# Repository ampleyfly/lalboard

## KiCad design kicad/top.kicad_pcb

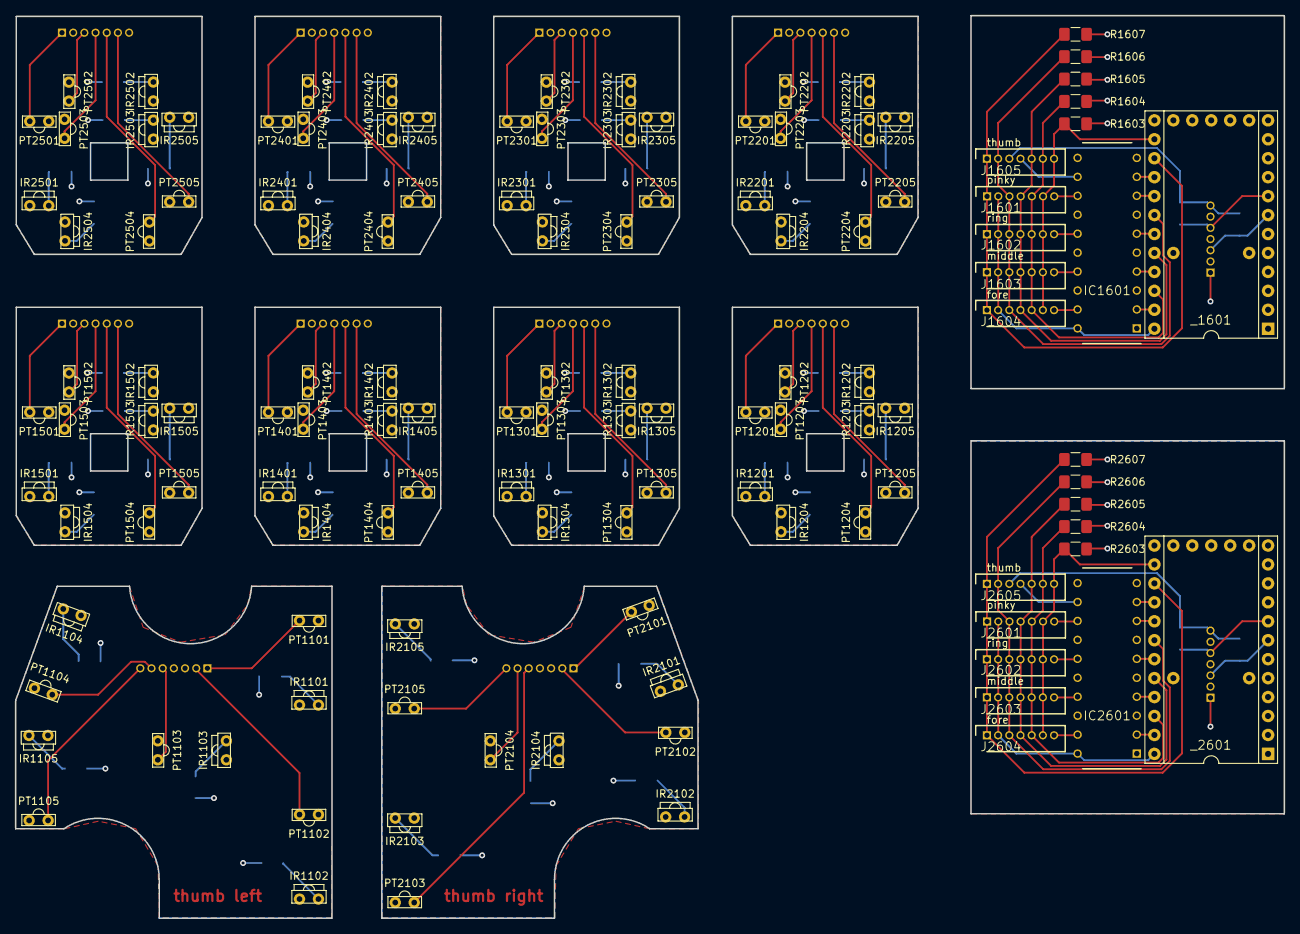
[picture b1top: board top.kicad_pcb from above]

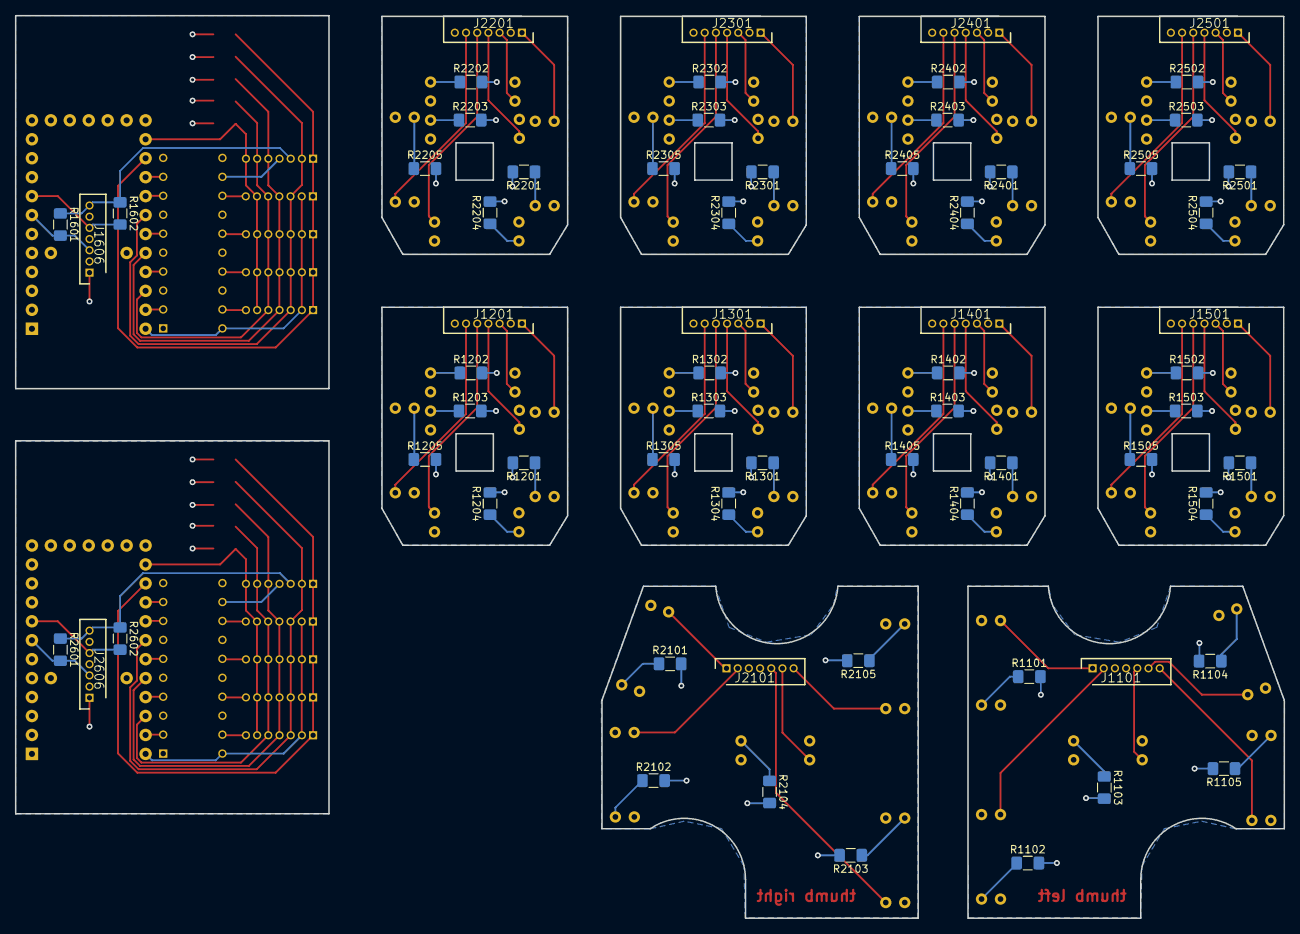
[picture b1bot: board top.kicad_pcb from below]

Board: 4 copper layers, 170.1 x 121.0 mm, 190 parts (66 on the bottom side), 160 nets.

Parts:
IC1601, IC2601: TLC59211IN; DIP794W53P254L2540H508Q20N
IR1101, IR1102, IR1103, IR1104, IR1105, IR1201, IR1202, IR1203, IR1204, IR1205, IR1301, IR1302, IR1303, IR1304, IR1305, IR1401, IR1402, IR1403, IR1404, IR1405, IR1501, IR1502, IR1503, IR1504, IR1505, IR2101, IR2102, IR2103, IR2104, IR2105, IR2201, IR2202, IR2203, IR2204, IR2205, IR2301, IR2302, IR2303, IR2304, IR2305, IR2401, IR2402, IR2403, IR2404, IR2405, IR2501, IR2502, IR2503, IR2504, IR2505: IR928-6C-F
J1101, J1201, J1301, J1401, J1501, J2101, J2201, J2301, J2401, J2501: Conn_01x07_Female; SHDR7W50P0X150_1X7_1200X350X45
J1601, J1602, J1603, J1604, J1605, J1606, J2601, J2602, J2603, J2604, J2605, J2606: B7B-ZR_(LF)(SN); SHDR7W50P0X150_1X7_1200X350X45
PT1101, PT1102, PT1103, PT1104, PT1105, PT1201, PT1202, PT1203, PT1204, PT1205, PT1301, PT1302, PT1303, PT1304, PT1305, PT1401, PT1402, PT1403, PT1404, PT1405, PT1501, PT1502, PT1503, PT1504, PT1505, PT2101, PT2102, PT2103, PT2104, PT2105, PT2201, PT2202, PT2203, PT2204, PT2205, PT2301, PT2302, PT2303, PT2304, PT2305, PT2401, PT2402, PT2403, PT2404, PT2405, PT2501, PT2502, PT2503, PT2504, PT2505: PT908-7B-F
R1101, R1102, R1103, R1104, R1105, R1201, R1202, R1203, R1204, R1205, R1301, R1302, R1303, R1304, R1305, R1401, R1402, R1403, R1404, R1405, R1501, R1502, R1503, R1504, R1505, R2101, R2102, R2103, R2104, R2105, R2201, R2202, R2203, R2204, R2205, R2301, R2302, R2303, R2304, R2305, R2401, R2402, R2403, R2404, R2405, R2501, R2502, R2503, R2504, R2505: 150; R_1206_3216Metric_Pad1.42x1.75mm_HandSolder
R1601, R1602, R1603, R1604, R1605, R1606, R1607, R2601, R2602, R2603, R2604, R2605, R2606, R2607: 2k; R_1206_3216Metric_Pad1.42x1.75mm_HandSolder
_1601, _2601: TEENSY

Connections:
/center_left/+5V: J1605.3, J1606.7, R1601.1, R1602.1, _1601.5V2
/center_left/F+5V: IC1601.20, J1601.2, J1602.2, J1603.2, J1604.2, _1601.+5V
/center_left/FD: J1601.4, J1602.4, J1603.4, J1604.4, J1605.5, R1605.1, _1601.F5
/center_left/FE: J1601.6, J1602.6, J1603.6, J1604.6, J1605.7, R1603.1, _1601.D7
/center_left/FGND: IC1601.19, J1604.7
/center_left/FN: J1601.3, J1602.3, J1603.3, J1604.3, J1605.2, R1606.1, _1601.F7
/center_left/FS: J1601.5, J1602.5, J1603.5, J1604.5, J1605.6, R1604.1, _1601.F1
/center_left/FW: J1601.1, J1602.1, J1603.1, J1604.1, J1605.1, R1607.1, _1601.B4
/center_left/GND: IC1601.3, IC1601.5, IC1601.7, IC1601.11, J1606.1, R1603.2, R1604.2, R1605.2, R1606.2, R1607.2, _1601.GND
/center_left/MGND: IC1601.17, J1603.7
/center_left/PGND: IC1601.13, J1601.7
/center_left/RGND: IC1601.15, J1602.7
/center_left/SCL: J1606.3, R1601.2, _1601.D0
/center_left/SDA: J1606.5, R1602.2, _1601.D1
/center_left/TGND: IC1601.12, J1605.4
/center_right/+5V: J2605.3, J2606.7, R2601.1, R2602.1, _2601.5V2
/center_right/F+5V: IC2601.20, J2601.2, J2602.2, J2603.2, J2604.2, _2601.+5V
/center_right/FD: J2601.4, J2602.4, J2603.4, J2604.4, J2605.5, R2605.1, _2601.F5
/center_right/FE: J2601.6, J2602.6, J2603.6, J2604.6, J2605.7, R2603.1, _2601.D7
/center_right/FGND: IC2601.19, J2604.7
/center_right/FN: J2601.3, J2602.3, J2603.3, J2604.3, J2605.2, R2606.1, _2601.F7
/center_right/FS: J2601.5, J2602.5, J2603.5, J2604.5, J2605.6, R2604.1, _2601.F1
/center_right/FW: J2601.1, J2602.1, J2603.1, J2604.1, J2605.1, R2607.1, _2601.B4
/center_right/GND: IC2601.3, IC2601.5, IC2601.7, IC2601.11, J2606.1, R2603.2, R2604.2, R2605.2, R2606.2, R2607.2, _2601.GND
/center_right/MGND: IC2601.17, J2603.7
/center_right/PGND: IC2601.13, J2601.7
/center_right/RGND: IC2601.15, J2602.7
/center_right/SCL: J2606.3, R2601.2, _2601.D0
/center_right/SDA: J2606.5, R2602.2, _2601.D1
/center_right/TGND: IC2601.12, J2605.4
/index_left/+5V: IR1201.2, IR1202.2, IR1203.2, IR1204.2, IR1205.2, J1201.2, PT1201.1, PT1202.1, PT1203.1, PT1204.1, PT1205.1
/index_left/D: J1201.4, PT1203.2
/index_left/E: J1201.6, PT1205.2
/index_left/GND: J1201.7, R1201.2, R1202.2, R1203.2, R1204.2, R1205.2
/index_left/N: J1201.3, PT1202.2
/index_left/S: J1201.5, PT1204.2
/index_left/W: J1201.1, PT1201.2
/index_right/+5V: IR2201.2, IR2202.2, IR2203.2, IR2204.2, IR2205.2, J2201.2, PT2201.1, PT2202.1, PT2203.1, PT2204.1, PT2205.1
/index_right/D: J2201.4, PT2203.2
/index_right/E: J2201.6, PT2205.2
/index_right/GND: J2201.7, R2201.2, R2202.2, R2203.2, R2204.2, R2205.2
/index_right/N: J2201.3, PT2202.2
/index_right/S: J2201.5, PT2204.2
/index_right/W: J2201.1, PT2201.2
/middle_left/+5V: IR1301.2, IR1302.2, IR1303.2, IR1304.2, IR1305.2, J1301.2, PT1301.1, PT1302.1, PT1303.1, PT1304.1, PT1305.1
/middle_left/D: J1301.4, PT1303.2
/middle_left/E: J1301.6, PT1305.2
/middle_left/GND: J1301.7, R1301.2, R1302.2, R1303.2, R1304.2, R1305.2
/middle_left/N: J1301.3, PT1302.2
/middle_left/S: J1301.5, PT1304.2
/middle_left/W: J1301.1, PT1301.2
/middle_right/+5V: IR2301.2, IR2302.2, IR2303.2, IR2304.2, IR2305.2, J2301.2, PT2301.1, PT2302.1, PT2303.1, PT2304.1, PT2305.1
/middle_right/D: J2301.4, PT2303.2
/middle_right/E: J2301.6, PT2305.2
/middle_right/GND: J2301.7, R2301.2, R2302.2, R2303.2, R2304.2, R2305.2
/middle_right/N: J2301.3, PT2302.2
/middle_right/S: J2301.5, PT2304.2
/middle_right/W: J2301.1, PT2301.2
/pinky_left/+5V: IR1501.2, IR1502.2, IR1503.2, IR1504.2, IR1505.2, J1501.2, PT1501.1, PT1502.1, PT1503.1, PT1504.1, PT1505.1
/pinky_left/D: J1501.4, PT1503.2
/pinky_left/E: J1501.6, PT1505.2
/pinky_left/GND: J1501.7, R1501.2, R1502.2, R1503.2, R1504.2, R1505.2
/pinky_left/N: J1501.3, PT1502.2
/pinky_left/S: J1501.5, PT1504.2
/pinky_left/W: J1501.1, PT1501.2
/pinky_right/+5V: IR2501.2, IR2502.2, IR2503.2, IR2504.2, IR2505.2, J2501.2, PT2501.1, PT2502.1, PT2503.1, PT2504.1, PT2505.1
/pinky_right/D: J2501.4, PT2503.2
/pinky_right/E: J2501.6, PT2505.2
/pinky_right/GND: J2501.7, R2501.2, R2502.2, R2503.2, R2504.2, R2505.2
/pinky_right/N: J2501.3, PT2502.2
/pinky_right/S: J2501.5, PT2504.2
/pinky_right/W: J2501.1, PT2501.2
/ring_left/+5V: IR1401.2, IR1402.2, IR1403.2, IR1404.2, IR1405.2, J1401.2, PT1401.1, PT1402.1, PT1403.1, PT1404.1, PT1405.1
/ring_left/D: J1401.4, PT1403.2
/ring_left/E: J1401.6, PT1405.2
/ring_left/GND: J1401.7, R1401.2, R1402.2, R1403.2, R1404.2, R1405.2
/ring_left/N: J1401.3, PT1402.2
/ring_left/S: J1401.5, PT1404.2
/ring_left/W: J1401.1, PT1401.2
/ring_right/+5V: IR2401.2, IR2402.2, IR2403.2, IR2404.2, IR2405.2, J2401.2, PT2401.1, PT2402.1, PT2403.1, PT2404.1, PT2405.1
/ring_right/D: J2401.4, PT2403.2
/ring_right/E: J2401.6, PT2405.2
/ring_right/GND: J2401.7, R2401.2, R2402.2, R2403.2, R2404.2, R2405.2
/ring_right/N: J2401.3, PT2402.2
/ring_right/S: J2401.5, PT2404.2
/ring_right/W: J2401.1, PT2401.2
/thumb_left/+5V: IR1101.2, IR1102.2, IR1103.2, IR1104.2, IR1105.2, J1101.3, PT1101.1, PT1102.1, PT1103.1, PT1104.1, PT1105.1
/thumb_left/D: J1101.5, PT1103.2
/thumb_left/GND: J1101.4, R1101.2, R1102.2, R1103.2, R1104.2, R1105.2
/thumb_left/I: J1101.6, PT1104.2
/thumb_left/LO: J1101.2, PT1102.2
/thumb_left/M: J1101.7, PT1105.2
/thumb_left/UO: J1101.1, PT1101.2
/thumb_right/+5V: IR2101.2, IR2102.2, IR2103.2, IR2104.2, IR2105.2, J2101.3, PT2101.1, PT2102.1, PT2103.1, PT2104.1, PT2105.1
/thumb_right/D: J2101.6, PT2104.2
/thumb_right/GND: J2101.4, R2101.2, R2102.2, R2103.2, R2104.2, R2105.2
/thumb_right/I: J2101.2, PT2102.2
/thumb_right/LO: J2101.5, PT2103.2
/thumb_right/M: J2101.1, PT2101.2
/thumb_right/UO: J2101.7, PT2105.2
unnamed: IC1601.2, _1601.F0
unnamed: IC1601.4, _1601.F4
unnamed: IC1601.6, _1601.F6
unnamed: IC1601.8, _1601.B6
unnamed: IC1601.9, _1601.B5
unnamed: IC2601.2, _2601.F0
unnamed: IC2601.4, _2601.F4
unnamed: IC2601.6, _2601.F6
unnamed: IC2601.8, _2601.B6
unnamed: IC2601.9, _2601.B5
unnamed: IR1101.1, R1101.1
unnamed: IR1102.1, R1102.1
unnamed: IR1103.1, R1103.1
unnamed: IR1104.1, R1104.1
unnamed: IR1105.1, R1105.1
unnamed: IR1201.1, R1201.1
unnamed: IR1202.1, R1202.1
unnamed: IR1203.1, R1203.1
unnamed: IR1204.1, R1204.1
unnamed: IR1205.1, R1205.1
unnamed: IR1301.1, R1301.1
unnamed: IR1302.1, R1302.1
unnamed: IR1303.1, R1303.1
unnamed: IR1304.1, R1304.1
unnamed: IR1305.1, R1305.1
unnamed: IR1401.1, R1401.1
unnamed: IR1402.1, R1402.1
unnamed: IR1403.1, R1403.1
unnamed: IR1404.1, R1404.1
unnamed: IR1405.1, R1405.1
unnamed: IR1501.1, R1501.1
unnamed: IR1502.1, R1502.1
unnamed: IR1503.1, R1503.1
unnamed: IR1504.1, R1504.1
unnamed: IR1505.1, R1505.1
unnamed: IR2101.1, R2101.1
unnamed: IR2102.1, R2102.1
unnamed: IR2103.1, R2103.1
unnamed: IR2104.1, R2104.1
unnamed: IR2105.1, R2105.1
unnamed: IR2201.1, R2201.1
unnamed: IR2202.1, R2202.1
unnamed: IR2203.1, R2203.1
unnamed: IR2204.1, R2204.1
unnamed: IR2205.1, R2205.1
unnamed: IR2301.1, R2301.1
unnamed: IR2302.1, R2302.1
unnamed: IR2303.1, R2303.1
unnamed: IR2304.1, R2304.1
unnamed: IR2305.1, R2305.1
unnamed: IR2401.1, R2401.1
unnamed: IR2402.1, R2402.1
unnamed: IR2403.1, R2403.1
unnamed: IR2404.1, R2404.1
unnamed: IR2405.1, R2405.1
unnamed: IR2501.1, R2501.1
unnamed: IR2502.1, R2502.1
unnamed: IR2503.1, R2503.1
unnamed: IR2504.1, R2504.1
unnamed: IR2505.1, R2505.1

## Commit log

2020-08-22 Import library from eagle center board
2020-08-22 Create library for everlight components
2020-08-27 WIP: Add kicad project
